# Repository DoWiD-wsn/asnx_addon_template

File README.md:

# ASN(x) Addon -- Environmental Monitoring

This branch contains the PCB files and other information related to the creation of own addon board for the **A**VR-based **S**ensor **N**ode with **X**bee, short **ASN(x)**, for environmental monitoring applications.
The Addon has a size of about 39 x 43.5 mm.
It contains an air temperature and relative humidity sensor, a light intensity sensor, and a air quality (gas) sensor.
All three sensors are supported by corresponding drivers in the ASN(x) library ([ASNX-LIB](https://github.com/DoWiD-wsn/avr-based_sensor_node/tree/master/source/_asnx_lib_/sensors)).

In particular, the used sensors are:

* [**SHT30-DIS-B**](docs/datasheets/sht30-dis-b.pdf), short ***SHT***: air temperature and relative humidity sensor (e.g., available at [Farnell](https://at.farnell.com/sensirion/sht30-dis-b/feuchtigkeits-temperatursensor/dp/2611275))
* [**BH1750FVI-TR**](docs/datasheets/bh1750fvi-tr.pdf), short ***BH***: light intensity sensor (e.g., available at [Farnell](https://at.farnell.com/rohm/bh1750fvi-tr/ambient-light-sensor-i2c-wsof/dp/2421284))
* [**ZMOD4410AI3V**](docs/datasheets/zmod4410ai3v.pdf), short ***ZMOD***: air quality (gas) sensor (e.g., available at [Farnell](https://at.farnell.com/integrated-device-technology/zmod4410ai3v/gassensormodul-tvoc-co2-ndir-5000ppm/dp/3588802))

## Contents

```
.
├── docs                : documents & project documentation
├── kicad               : KiCad files
├── media               : Miscellaneous media (images, etc.)
    ├── pcb             : Photos and rendered images of the PCB
    └── schematic       : SVG images of the schematics
```

For more information on the PCB (and its design) refer to [docs/pcb_design.md](docs/pcb_design.md).

## Built with

* [KiCad EAD 5.1.9](https://kicad.org/) - PCB design

## Contributors

* **Dominik Widhalm** - [***DC-RES***](https://informatics.tuwien.ac.at/doctoral/resilient-embedded-systems/) - [*UAS Technikum Wien*](https://embsys.technikum-wien.at/staff/widhalm/)

Contributions of any kind to improve the project are highly welcome.
For coding bugs or minor improvements simply use pull requests.
However, for major changes or general discussions please contact [Dominik Widhalm](mailto:widhalm@technikum-wien.at?subject=ASN(x)%20on%20GitHub).

## Changelog

A list of prior versions and changes between the updates can be found inn the [CHANGELOG.md](CHANGELOG.md) file.
Note that the major and minor number refer to the hardware version of the ASN(x) addon template while the patch version is not used in this project.

## License

This project is licensed under the MIT License - see the [LICENSE.md](LICENSE.md) file for details.

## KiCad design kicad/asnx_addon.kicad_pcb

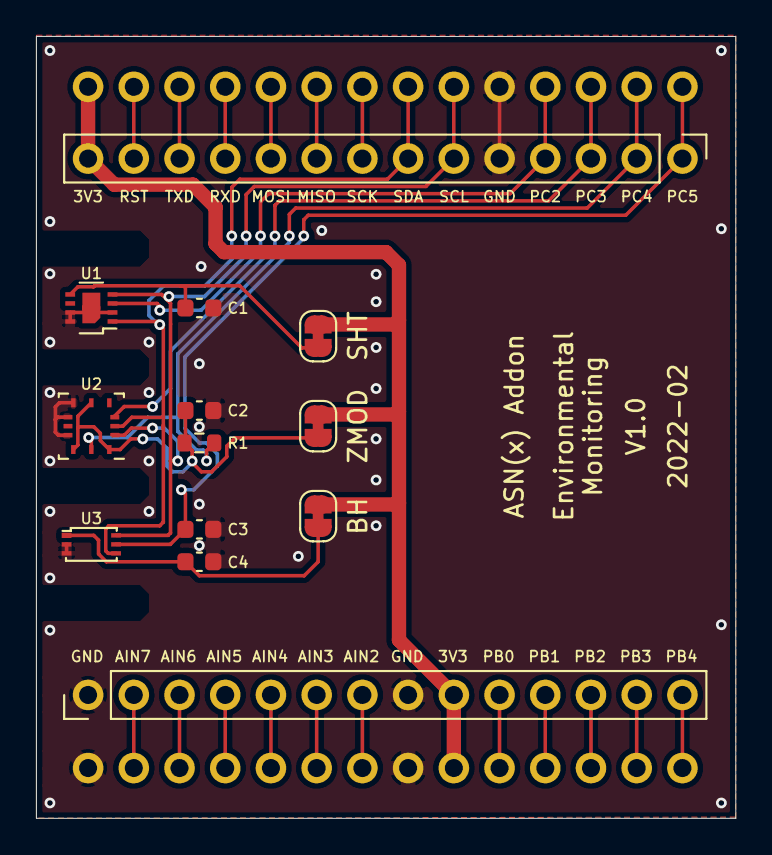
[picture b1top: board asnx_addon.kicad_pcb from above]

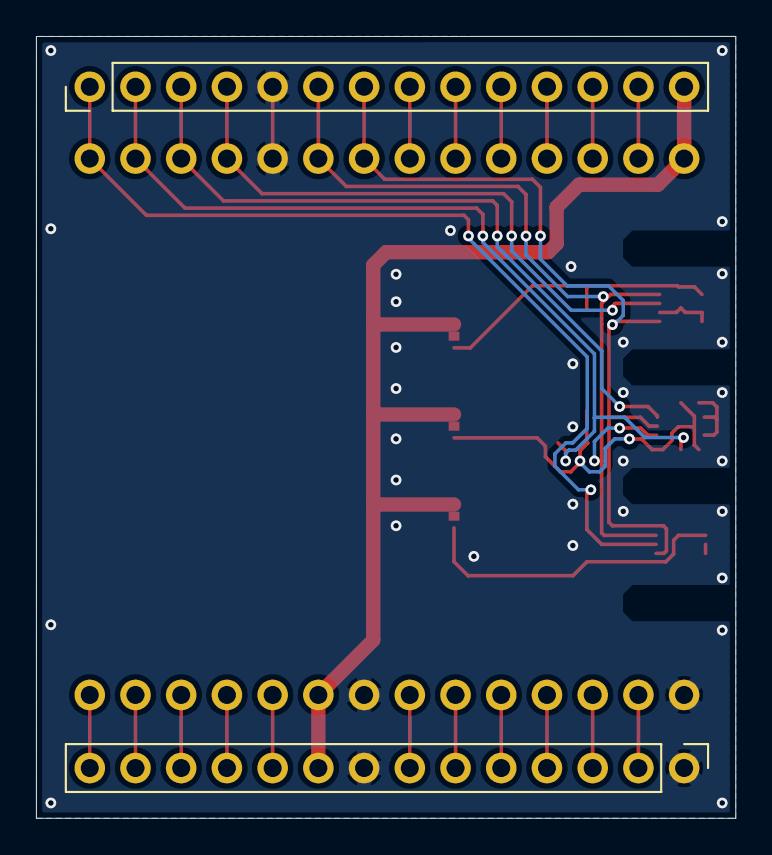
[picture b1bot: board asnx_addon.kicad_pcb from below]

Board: 2 copper layers, 38.8 x 43.4 mm, 15 parts (2 on the bottom side), 28 nets.

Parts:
C1, C2, C3, C4: 100n; C_0603_1608Metric
J1, J2: COM/GPIO; PinHeader_1x14_P2.54mm_Vertical
J3, J4: ADC/GPIO; PinHeader_1x14_P2.54mm_Vertical
JP1: EN_SHT; SolderJumper-2_P1.3mm_Bridged_RoundedPad1.0x1.5mm
JP2: EN_ZMOD; SolderJumper-2_P1.3mm_Bridged_RoundedPad1.0x1.5mm
JP3: EN_BH; SolderJumper-2_P1.3mm_Bridged_RoundedPad1.0x1.5mm
R1: 4k7; R_0603_1608Metric
U1: SHT30-DIS; Sensirion_DFN-8-1EP_2.5x2.5mm_P0.5mm_EP1.1x1.7mm
U2: ZMOD4410; ZMOD4410-12-LGA
U3: BH1750FVI; BH1750FVI-WSOF6I

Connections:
+3V3: J1.14, J2.14, J3.9, J4.9, JP1.1, JP2.1, JP3.1
/ADC2: J3.7, J4.7
/ADC3: J3.6, J4.6
/ADC4: J3.5, J4.5
/ADC5: J3.4, J4.4
/ADC6: J3.3, J4.3
/ADC7: J3.2, J4.2
/BH_PWR: C4.1, JP3.2, U3.1
/I2C_SCL: J1.6, J2.6, U1.4, U2.1, U3.6
/I2C_SDA: J1.7, J2.7, U1.1, U2.2, U3.4
/PB0: J3.10, J4.10
/PB1: J3.11, J4.11
/PB2: J3.12, J4.12
/PB3: J3.13, J4.13
/PB4: J3.14, J4.14
/PC2: J1.4, J2.4, U1.3
/PC3: J1.3, J2.3, U2.3
/PC4: J1.2, J2.2, R1.2, U2.11
/PC5: C3.1, J1.1, J2.1, U3.5
/RESET: J1.13, J2.13
/RXD1: J1.11, J2.11
/SHT_PWR: C1.1, JP1.2, U1.5
/SPI_MISO: J1.9, J2.9
/SPI_MOSI: J1.10, J2.10
/SPI_SCK: J1.8, J2.8
/TXD1: J1.12, J2.12
/ZMOD_PWR: C2.1, JP2.2, R1.1, U2.5, U2.10, U2.12
GND: C1.2, C2.2, C3.2, C4.2, J1.5, J2.5, J3.1, J3.8, J4.1, J4.8, U1.2, U1.7, U1.8, U1.9, U2.6, U2.7, U2.9, U3.2, U3.3

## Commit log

2021-07-08 Initial commit: added superior gitignore
2021-07-08 Added initial README, the initial CHANGELOG and the MIT license file
2021-07-08 Changed name in license file
2021-07-08 Added initial version of addon board PCB design
2021-11-08 Change license extension to md
2021-11-18 Changed license file extension to markdown
2022-02-23 Started with environmental monitoring sensor addon (schematic done; PCB to do)
2022-02-24 Added initial PCB design (incl. BOM)
2022-02-25 Refined EM addon and added BOM
2022-02-27 Updated environmental monitoring addon and related information
2022-02-27 Updated PCB design documentation
2022-02-27 Added missing board measurements
2022-04-12 Added sensor datasheets
2022-04-12 Extended README with sensor information
2022-04-12 Added sensor abbreviations in README as used on PCB
